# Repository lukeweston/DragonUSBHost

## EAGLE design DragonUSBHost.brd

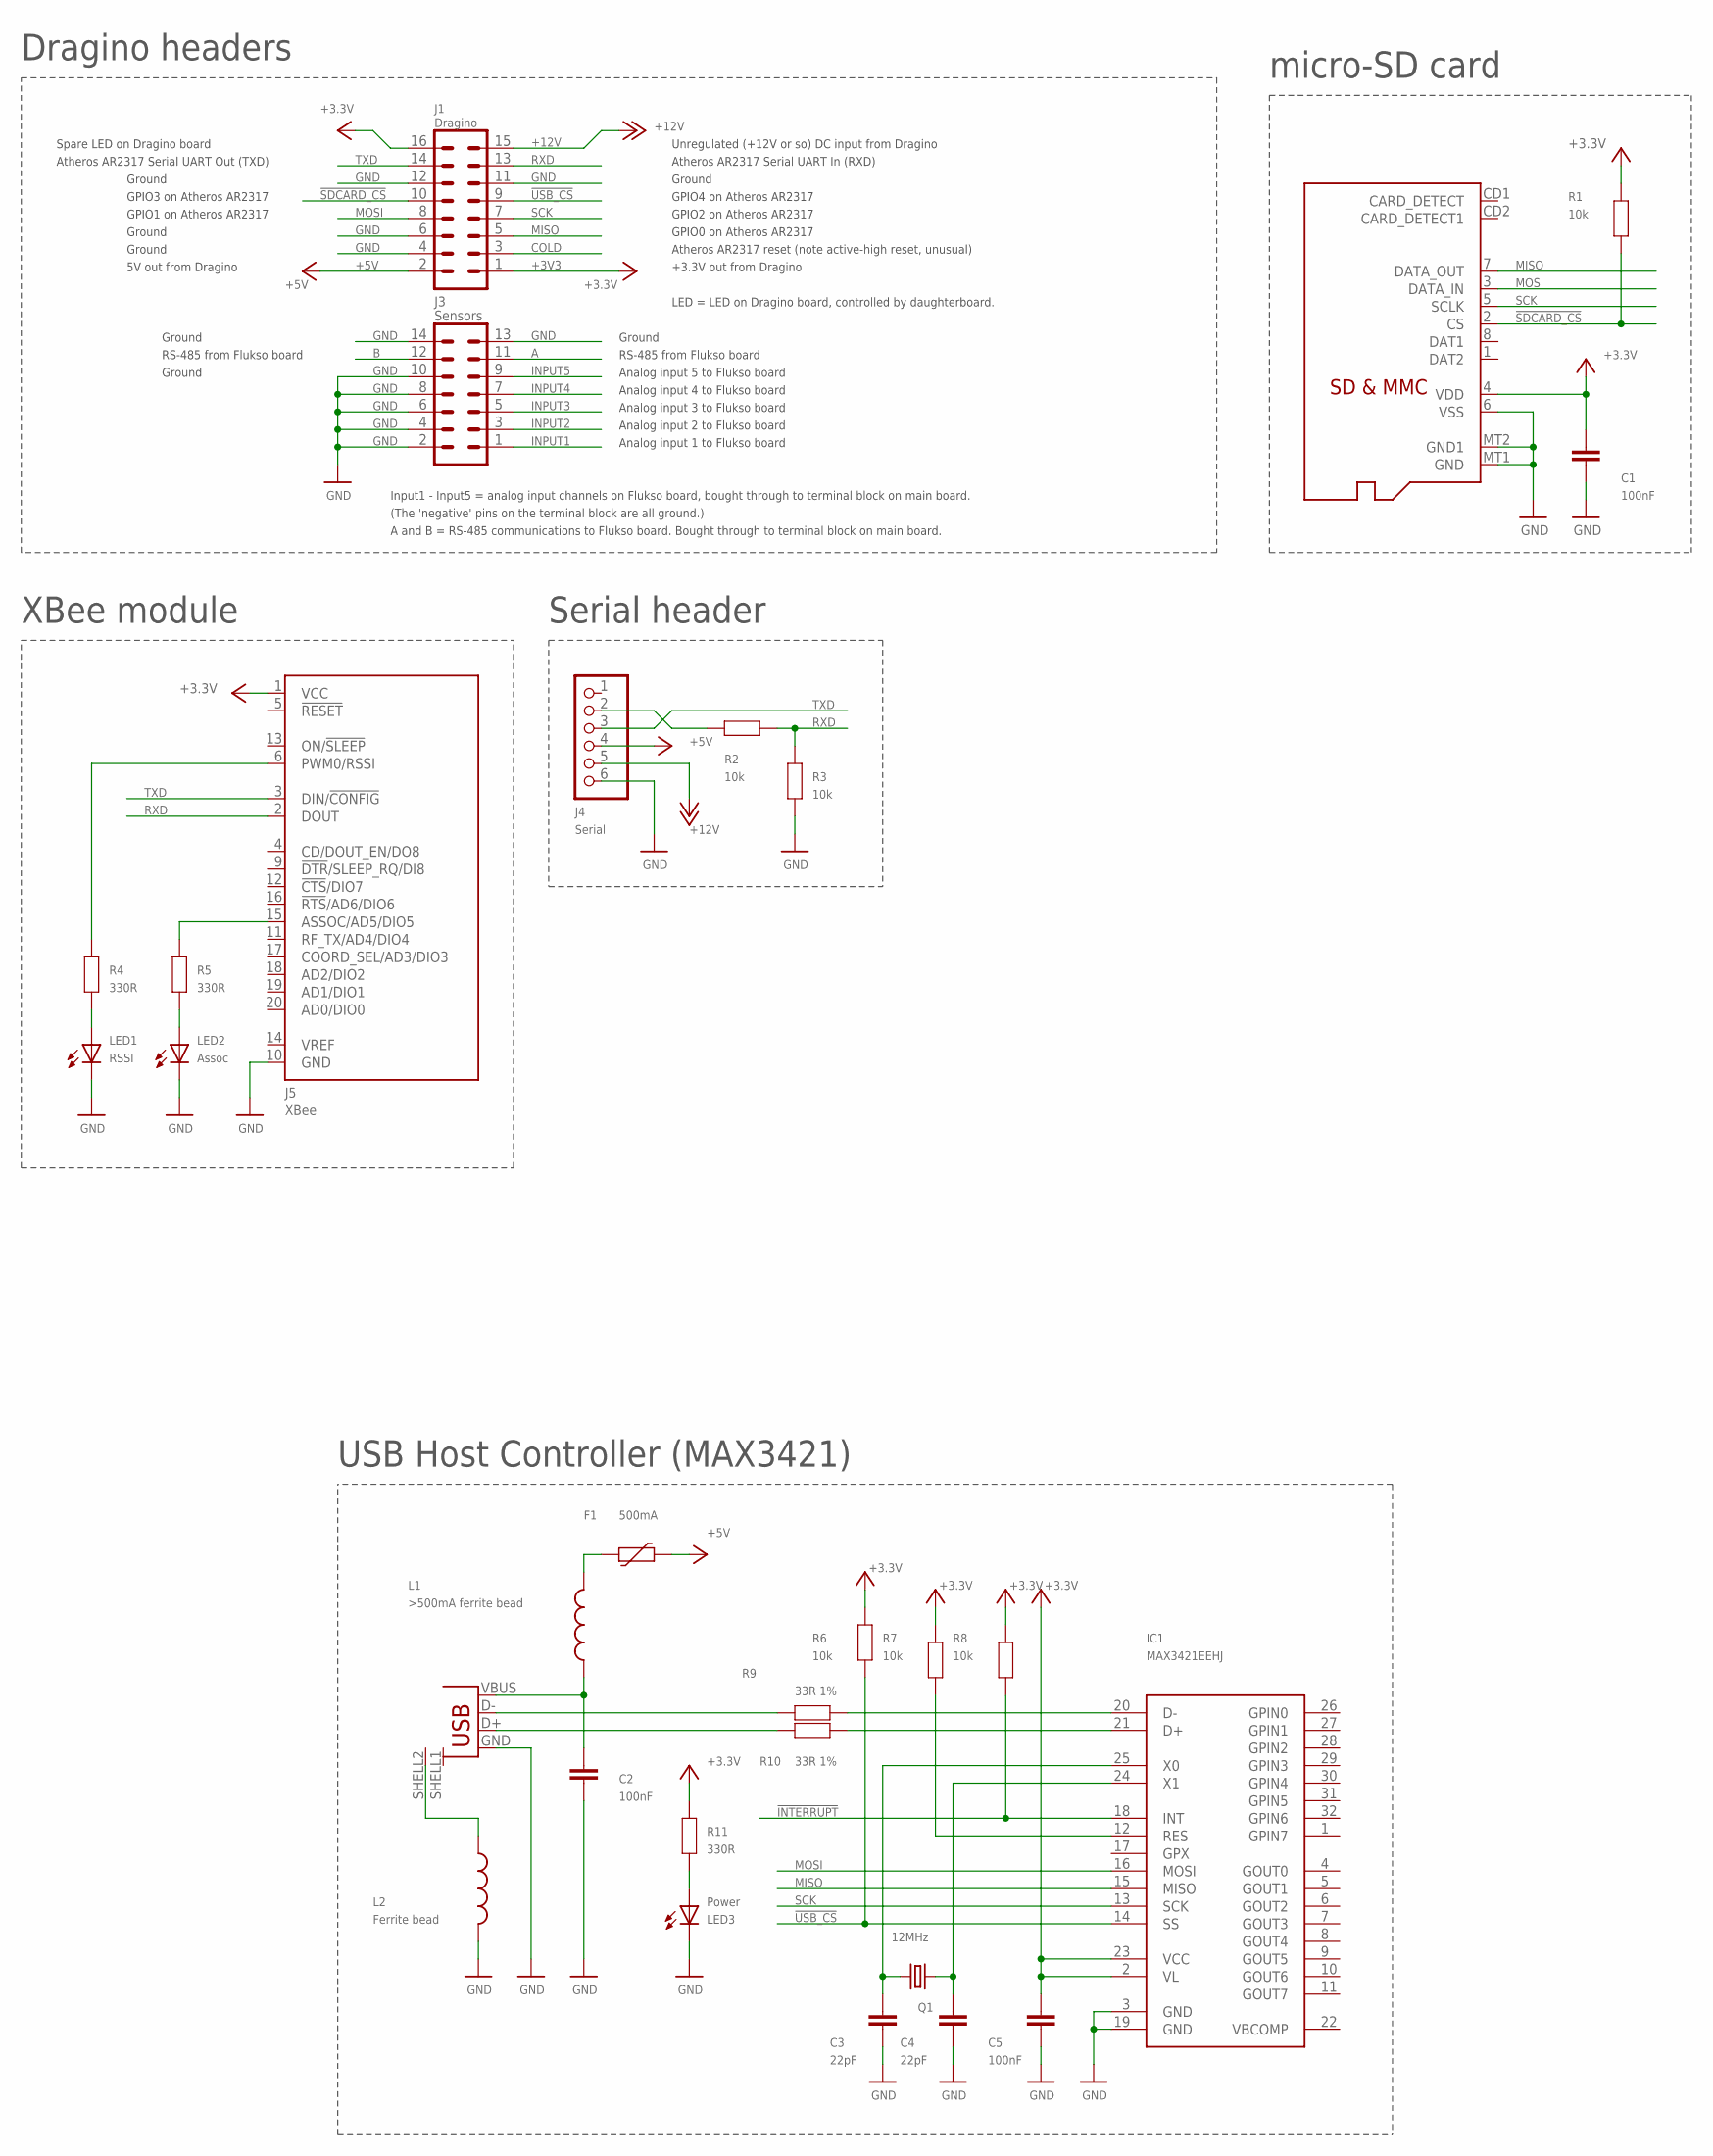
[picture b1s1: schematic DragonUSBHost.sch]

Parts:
C1, C2, C5: 100nF; 0805
C3, C4: 22pF; 0805
F1: 500mA; 1812
IC1: MAX3421EEHJ; TQFP32-5MM
J1: Dragino; MA08-2
J2: MICROSD
J3: Sensors; MA07-2
J4: Serial; 1X06
J5: XBee; XBEE-PRO
L1: >500mA ferrite bead; 0805-LARGE
L2: Ferrite bead; 0805-LARGE
LED1: RSSI; LED-0805
LED2: Assoc; LED-0805
LED3: Power; LED-0805
P1: USB_; USB-A-S-SILK-FEMALE
Q1: 12MHz; CRYSTAL-SMD-5X3
R1, R2, R3, R6, R7, R8: 10k; 0805
R4, R5, R11: 330R; 0805
R9, R10: 33R 1%; 0805

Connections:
!INTERRUPT: IC1.18 (INT), R8.1
!RESET: IC1.12 (RES), R7.1
!SDCARD_CS: J1.10, J2.2 (CS), R1.1
!USB_CS: IC1.14 (SS), J1.9, R6.1
+3V3: C1.1, C5.1, IC1.2 (VL), IC1.23 (VCC), J1.1, J1.16, J2.4 (VDD), J5.1 (VCC), R1.2, R6.2, R7.2, R8.2, R11.2
+5V: F1.2, J1.2, J4.4
+12V: J1.15, J4.5
A: J3.11
B: J3.12
COLD: J1.3
GND: C1.2, C2.1, C3.2, C4.2, C5.2, IC1.3 (GND), IC1.19 (GND), J1.4, J1.6, J1.11, J1.12, J2.6 (VSS), J2.MT1 (GND), J2.MT2 (GND1), J3.2, J3.4, J3.6, J3.8, J3.10, J3.13, J3.14, J4.6, J5.10 (GND), L2.2, LED1.C, LED2.C, LED3.C, P1.GND, R3.1
INPUT1: J3.1
INPUT2: J3.3
INPUT3: J3.5
INPUT4: J3.7
INPUT5: J3.9
MISO: IC1.15 (MISO), J1.5, J2.7 (DATA_OUT)
MOSI: IC1.16 (MOSI), J1.8, J2.3 (DATA_IN)
unnamed: P1.D-, R9.2
unnamed: L2.1, P1.SHELL2
unnamed: P1.D+, R10.2
unnamed: C2.2, L1.1, P1.VBUS
unnamed: IC1.20 (D-), R9.1
unnamed: LED2.A, R5.1
unnamed: J5.15 (ASSOC/AD5/DIO5), R5.2
unnamed: IC1.21 (D+), R10.1
unnamed: LED1.A, R4.1
unnamed: J5.6 (PWM0/RSSI), R4.2
unnamed: J4.2, R2.2
unnamed: C3.1, IC1.25 (X0), Q1.3 (2)
unnamed: C4.1, IC1.24 (X1), Q1.1
unnamed: LED3.A, R11.1
RXD: J1.13, J5.2 (DOUT), R2.1, R3.2
SCK: IC1.13 (SCK), J1.7, J2.5 (SCLK)
TXD: J1.14, J4.3, J5.3 (DIN/!CONFIG)
VBUS: F1.1, L1.2

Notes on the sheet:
A and B = RS-485 communications to Flukso board. Bought through to terminal block on main board.
Input1 - Input5 = analog input channels on Flukso board, bought through to terminal block on main board.
(The 'negative' pins on the terminal block are all ground.)
RS-485 from Flukso board
Analog input 5 to Flukso board
+3.3V out from Dragino
GPIO0 on Atheros AR2317
GPIO2 on Atheros AR2317
GPIO4 on Atheros AR2317
GPIO3 on Atheros AR2317
GPIO1 on Atheros AR2317
5V out from Dragino
Analog input 4 to Flukso board
Analog input 3 to Flukso board
Analog input 2 to Flukso board
Analog input 1 to Flukso board
Spare LED on Dragino board
Atheros AR2317 Serial UART Out (TXD)
Atheros AR2317 Serial UART In (RXD)
Unregulated (+12V or so) DC input from Dragino
Atheros AR2317 reset (note active-high reset, unusual)
Ground
LED = LED on Dragino board, controlled by daughterboard.
Dragino headers
XBee module
micro-SD card
Serial header
USB Host Controller (MAX3421)

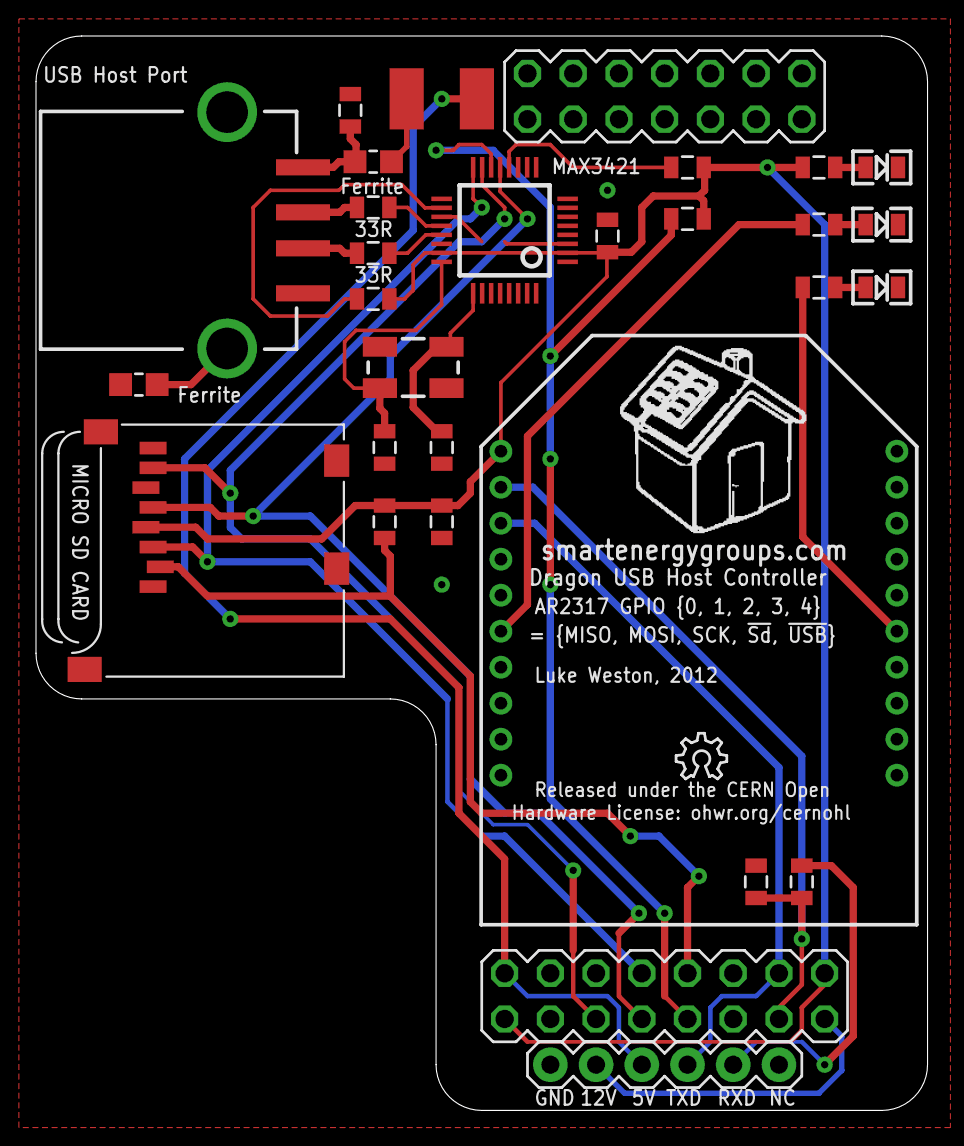
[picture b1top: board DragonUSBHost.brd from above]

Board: 2 copper layers, 49.5 x 59.7 mm, 31 parts (0 on the bottom side), 28 nets.

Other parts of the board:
U$21: OSHW_6X100_NOTEXT

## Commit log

2012-07-22 added readme

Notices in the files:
DragonUSBHost.brd:
Hardware License: ohwr.org/cernohl
DragonUSBHost.sch:
Released under CERN OHL:
